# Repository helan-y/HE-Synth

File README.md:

# HE Synth

## About
A custom, compact, modular velocity-sensitive digital synthesizer, made with Hall-Effect keyswitches and DaisySeed. 

## Idea
I want to make music and I do not have money but I do have blood, sweat, and many, many tears. This is also a proof of concept towards bigger projects I want to make in the future!
- MIDI keyboard with trackballs for keys! like a roli seaboard but weird and isomorphic! what if piano could vibrato!!
- bigger modular midi (repeating pcb boards in series one for each octave) keyboard with keycaps like piano keys!
- sampler! vocoder! etc!

## Features
Hardware features:
- Velocity-sensitive! Aftertouch! Two/three/more octaves!
- Fully **modular**. Add more octaves, swap out MIDI controllers, swap out the synthesizer. Assembled with separate custom PCB boards for maximum customizability. 
- In-build audio! 3.5 mm headphone jack or speaker. 

Constantly updating firmware:
- Different presets! Different sound envelopes!
- There's even a looper!
- And a display!

## PCB
The PCB design is divided into four parts:
1. Main Board
2. Power Distribution Board (PDB)
3. Octave PCBs
    - 12 Hall-Effect Keyswitches
    - STM32 MCU Chip
    - UART data transmission
4. MIDI-Out PCB
    - ESP32
    - MIDI OUT
    - USB-C

### Main Board
- Contains the Daisy Seed
- Switches, rotary encoders, and potentiometers
- Display with microSD card
- Ports!
    - MIDI IN
    - AUDIO IN x2
    - AUDIO OUT x2
    - 3.5mm Headphone Jack
    - microUSB for programming the Daisy
    - USB-C for data

### PDB
- USB-C charging
- Battery management
- 6000 mAh Li-Po
- Boost to 5V
- Buck-Boost to 3V3

### Octave PCB
An octave of velocity-sensitive keys. Hall-effect sensors, processed into usable data for the Daisy Seed. 
- 12 Hall-Effect Keyswitches
- STM32 MCU Chip
- UART data transmission

### MIDI-Out PCB
- ESP32
- MIDI OUT
- USB-C

## CAD

## Firmware
Firmware coded with C++ and libraries libDaisy and daisySP. 

## BOM
### Main PCB
- 1x Electro-Smith Daisy Seed
- 2x EC11 Rotary Encoders
- 6x Cherry MX Keyswitches
- 9x Potentiometers
- 1x 3-pin Male Header JST-PH
- 1x 10-pin JST
- 1x 4-pin Male Header JST-PH
- 2x DIN-5 MIDI Jack
- 1x 3.5mm Headphone Jack
- 2x PJ-320 Jacks
- 1x Optocoupler
- 1x Speaker

### Octave PCB 
- 12x Gateron Jade Magnetic Switches
- 12x Linear Hall-Effect Sensors
- 1x STM32
- 12x 0.1uF Capacitors
- 1x 2-Pin Male Header JST-PH 
- 1x 4-Pin Male Header JST-PH
- 1x RS-485
- 1x 3-Bit DIP Switch

Three of these for this particular iteration!

### Power Distribution Board
- 1x USB-C Receptacle
- 3x 2-Pin Male Header JST-PH
- 1x 3-Pin Male Header JST-PH
-

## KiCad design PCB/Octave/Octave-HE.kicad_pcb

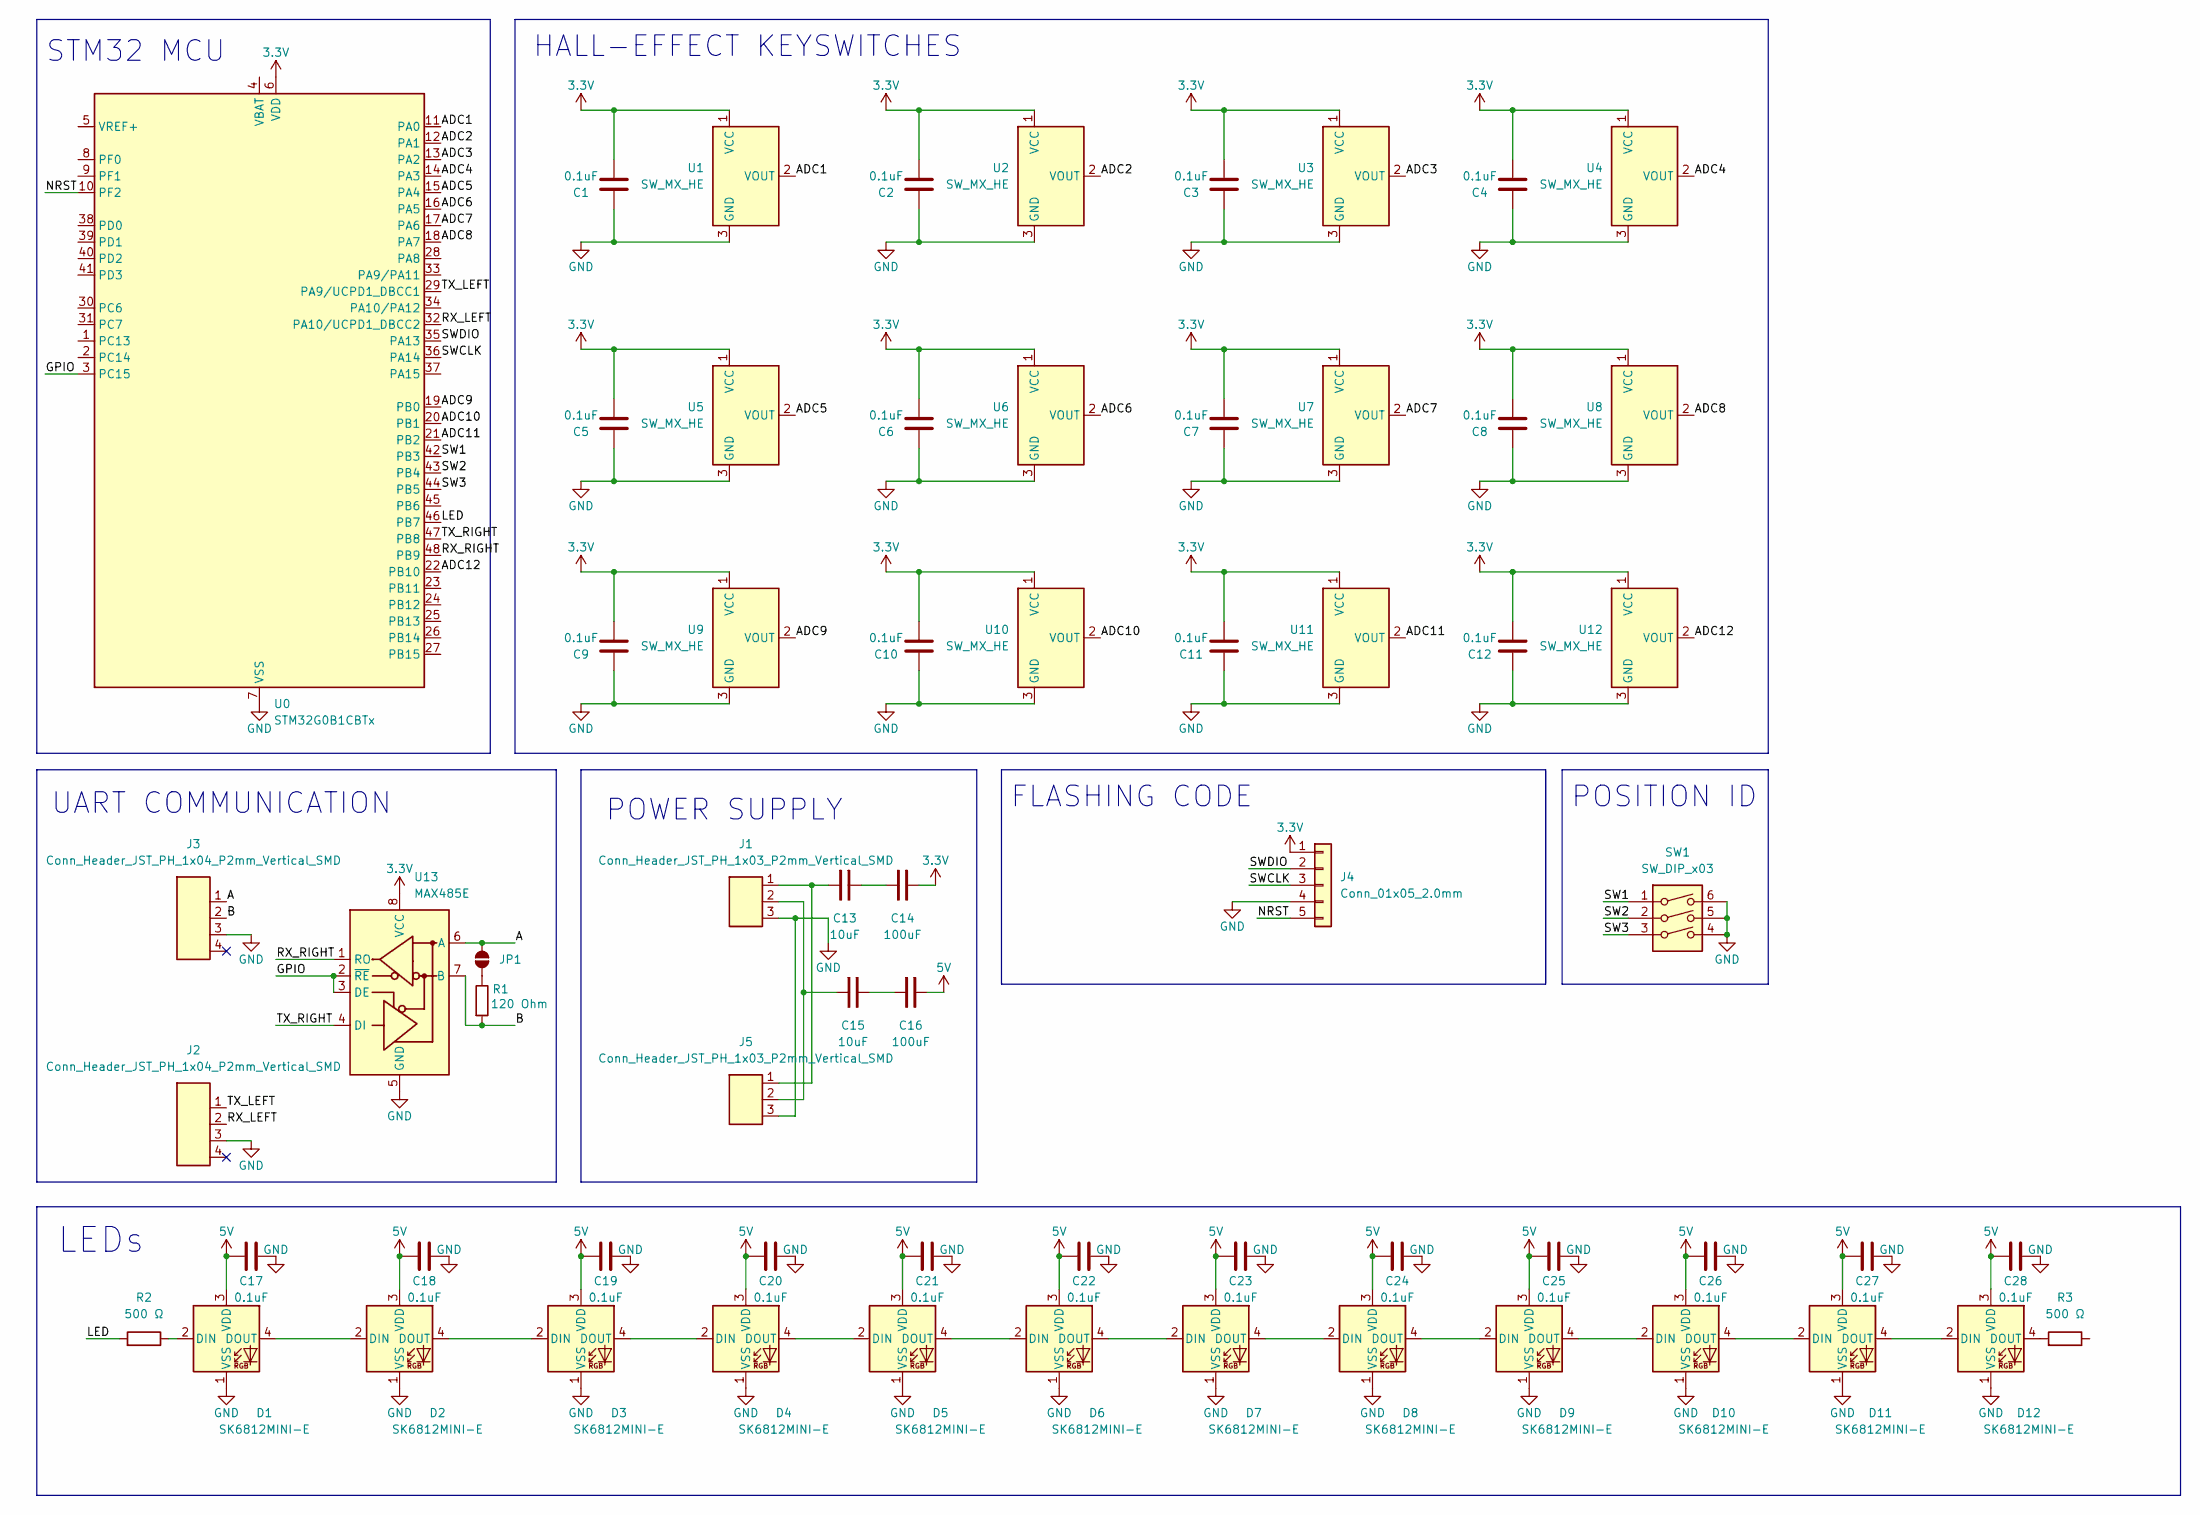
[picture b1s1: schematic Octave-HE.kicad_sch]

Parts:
C1, C2, C3, C4, C5, C6, C7, C8, C9, C10, C11, C12, C17, C18, C19, C20, C21, C22, C23, C24, C25, C26, C27, C28: 0.1uF; C_0201_0603Metric_Clearance
C13, C15: 10uF; CP_EIA-3216-10_Kemet-I_HandSolder
C14, C16: 100uF; CP_EIA-3216-10_Kemet-I_HandSolder
D1, D2, D3, D4, D5, D6, D7, D8, D9, D10, D11, D12: SK6812MINI-E; LED_SK6812MINI-E_3.2x2.8mm_P1.5mm_ReverseMount_clearance
J1, J5: Conn_Header_JST_PH_1x03_P2mm_Vertical_SMD; Header_JST_PH_1x03_P2mm_Vertical_SMD
J2, J3: Conn_Header_JST_PH_1x04_P2mm_Vertical_SMD; Header_JST_PH_1x04_P2mm_Vertical_SMD
J4: Conn_01x05_2.0mm; 1x05_P2.0mm_Socket_Vertical_SMD_Pin1RightDown
JP1: Jumper_2_NO
R1: 120 Ohm; R_0201_0603Metric
R2, R3: 500 Ω; R_0402_1005Metric
SW1: SW_DIP_x03; SW_DIP_SPSTx03_Slide_6.7x9.18mm_W6.73mm_P2.54mm_LowProfile_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
U0: STM32G0B1CBTx; LQFP-48_7x7mm_P0.5mm
U1, U2, U3, U4, U5, U6, U7, U8, U9, U10, U11, U12: SW_MX_HE; SW_MX_HE_0deg_1u
U13: MAX485E; SOIC-8_3.9x4.9mm_P1.27mm

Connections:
3.3V: C1.2, C2.2, C3.2, C4.2, C5.2, C6.2, C7.2, C8.2, C9.2, C10.2, C11.2, C12.2, C14.2, J4.1, U0.6 (VDD), U1.1 (VCC), U2.1 (VCC), U3.1 (VCC), U4.1 (VCC), U5.1 (VCC), U6.1 (VCC), U7.1 (VCC), U8.1 (VCC), U9.1 (VCC), U10.1 (VCC), U11.1 (VCC), U12.1 (VCC), U13.8 (VCC)
5V: C16.2, C17.2, C18.2, C19.2, C20.2, C21.2, C22.2, C23.2, C24.2, C25.2, C26.2, C27.2, C28.2, D1.3 (VDD), D2.3 (VDD), D3.3 (VDD), D4.3 (VDD), D5.3 (VDD), D6.3 (VDD), D7.3 (VDD), D8.3 (VDD), D9.3 (VDD), D10.3 (VDD), D11.3 (VDD), D12.3 (VDD)
/A: J3.1, JP1.2 (B), U13.6 (A)
/ADC1: U0.11 (PA0), U1.2 (VOUT)
/ADC2: U0.12 (PA1), U2.2 (VOUT)
/ADC3: U0.13 (PA2), U3.2 (VOUT)
/ADC4: U0.14 (PA3), U4.2 (VOUT)
/ADC5: U0.15 (PA4), U5.2 (VOUT)
/ADC6: U0.16 (PA5), U6.2 (VOUT)
/ADC7: U0.17 (PA6), U7.2 (VOUT)
/ADC8: U0.18 (PA7), U8.2 (VOUT)
/ADC9: U0.19 (PB0), U9.2 (VOUT)
/ADC10: U0.20 (PB1), U10.2 (VOUT)
/ADC11: U0.21 (PB2), U11.2 (VOUT)
/ADC12: U0.22 (PB10), U12.2 (VOUT)
/B: J3.2, R1.1, U13.7 (B)
/GPIO: U0.3 (PC15), U13.2 (~RE), U13.3 (DE)
/LED: R2.1, U0.46 (PB7)
/NRST: J4.5, U0.10 (PF2)
/RX_LEFT: J2.2, U0.32 (PA10/UCPD1_DBCC2)
/RX_RIGHT: U0.48 (PB9), U13.1 (RO)
/SW1: SW1.1, U0.42 (PB3)
/SW2: SW1.2, U0.43 (PB4)
/SW3: SW1.3, U0.44 (PB5)
/SWCLK: J4.3, U0.36 (PA14)
/SWDIO: J4.2, U0.35 (PA13)
/TX_LEFT: J2.1, U0.29 (PA9/UCPD1_DBCC1)
/TX_RIGHT: U0.47 (PB8), U13.4 (DI)
GND: C1.1, C2.1, C3.1, C4.1, C5.1, C6.1, C7.1, C8.1, C9.1, C10.1, C11.1, C12.1, C17.1, C18.1, C19.1, C20.1, C21.1, C22.1, C23.1, C24.1, C25.1, C26.1, C27.1, C28.1, D1.1 (VSS), D2.1 (VSS), D3.1 (VSS), D4.1 (VSS), D5.1 (VSS), D6.1 (VSS), D7.1 (VSS), D8.1 (VSS), D9.1 (VSS), D10.1 (VSS), D11.1 (VSS), D12.1 (VSS), J1.3, J2.3, J3.3, J4.4, J5.3, SW1.4, SW1.5, SW1.6, U0.7 (VSS), U1.3 (GND), U2.3 (GND), U3.3 (GND), U4.3 (GND), U5.3 (GND), U6.3 (GND), U7.3 (GND), U8.3 (GND), U9.3 (GND), U10.3 (GND), U11.3 (GND), U12.3 (GND), U13.5 (GND)
unnamed: C13.1, J1.1, J5.1
unnamed: C13.2, C14.1
unnamed: C15.1, J1.2, J5.2
unnamed: C15.2, C16.1
unnamed: D1.2 (DIN), R2.2
unnamed: D1.4 (DOUT), D2.2 (DIN)
unnamed: D2.4 (DOUT), D3.2 (DIN)
unnamed: D3.4 (DOUT), D4.2 (DIN)
unnamed: D4.4 (DOUT), D5.2 (DIN)
unnamed: D5.4 (DOUT), D6.2 (DIN)
unnamed: D6.4 (DOUT), D7.2 (DIN)
unnamed: D7.4 (DOUT), D8.2 (DIN)
unnamed: D8.4 (DOUT), D9.2 (DIN)
unnamed: D9.4 (DOUT), D10.2 (DIN)
unnamed: D10.4 (DOUT), D11.2 (DIN)
unnamed: D11.4 (DOUT), D12.2 (DIN)
unnamed: D12.4 (DOUT), R3.1
unnamed: JP1.1 (A), R1.2

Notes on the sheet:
HALL-EFFECT KEYSWITCHES
LEDs
POSITION ID
STM32 MCU
UART COMMUNICATION
FLASHING CODE
POWER SUPPLY

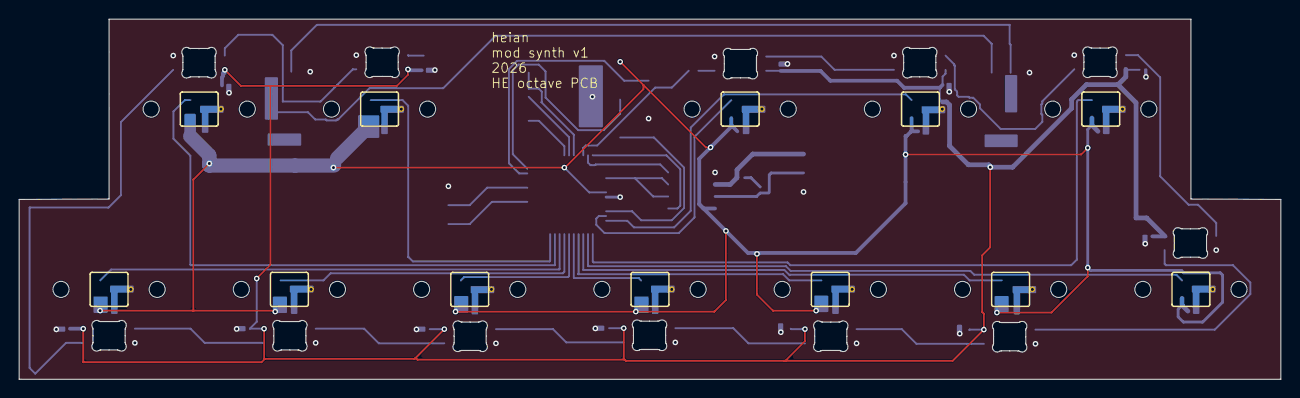
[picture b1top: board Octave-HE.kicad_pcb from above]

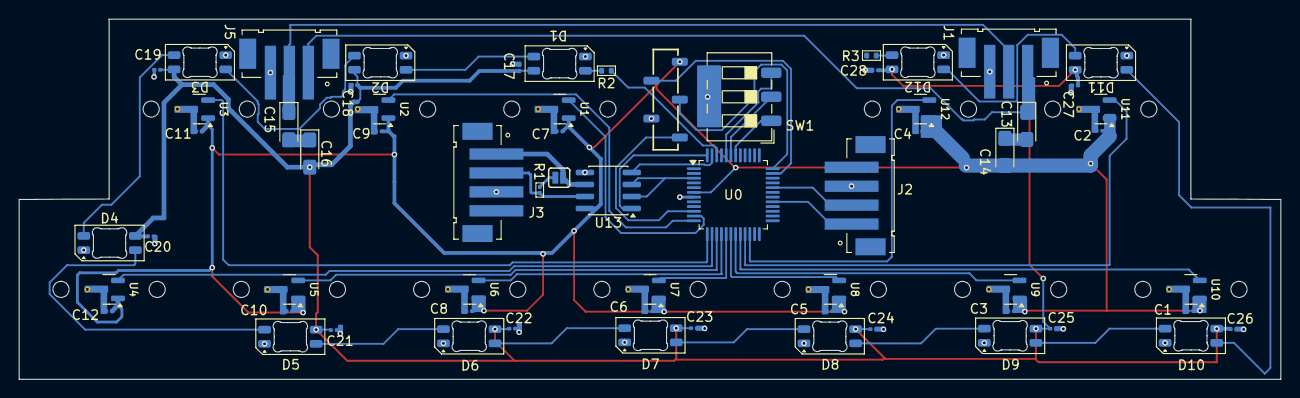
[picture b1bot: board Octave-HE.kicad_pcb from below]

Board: 2 copper layers, 133.2 x 38.0 mm, 64 parts (64 on the bottom side), 47 nets.

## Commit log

2026-06-11 readme init
2026-06-12 actual readme initial?
2026-06-13 read me schematic started
2026-06-13 small fix
2026-06-13 read me schematic updates
2026-06-13 readme
    Updated the description of the synthesizer to include 'modular'.
2026-06-13 readme
2026-06-14 read me bom updates
2026-06-15 readme and journal
2026-06-18 octave PCB done
2026-06-24 Add GNU General Public License v3
    Added the GNU General Public License version 3 to the project.
